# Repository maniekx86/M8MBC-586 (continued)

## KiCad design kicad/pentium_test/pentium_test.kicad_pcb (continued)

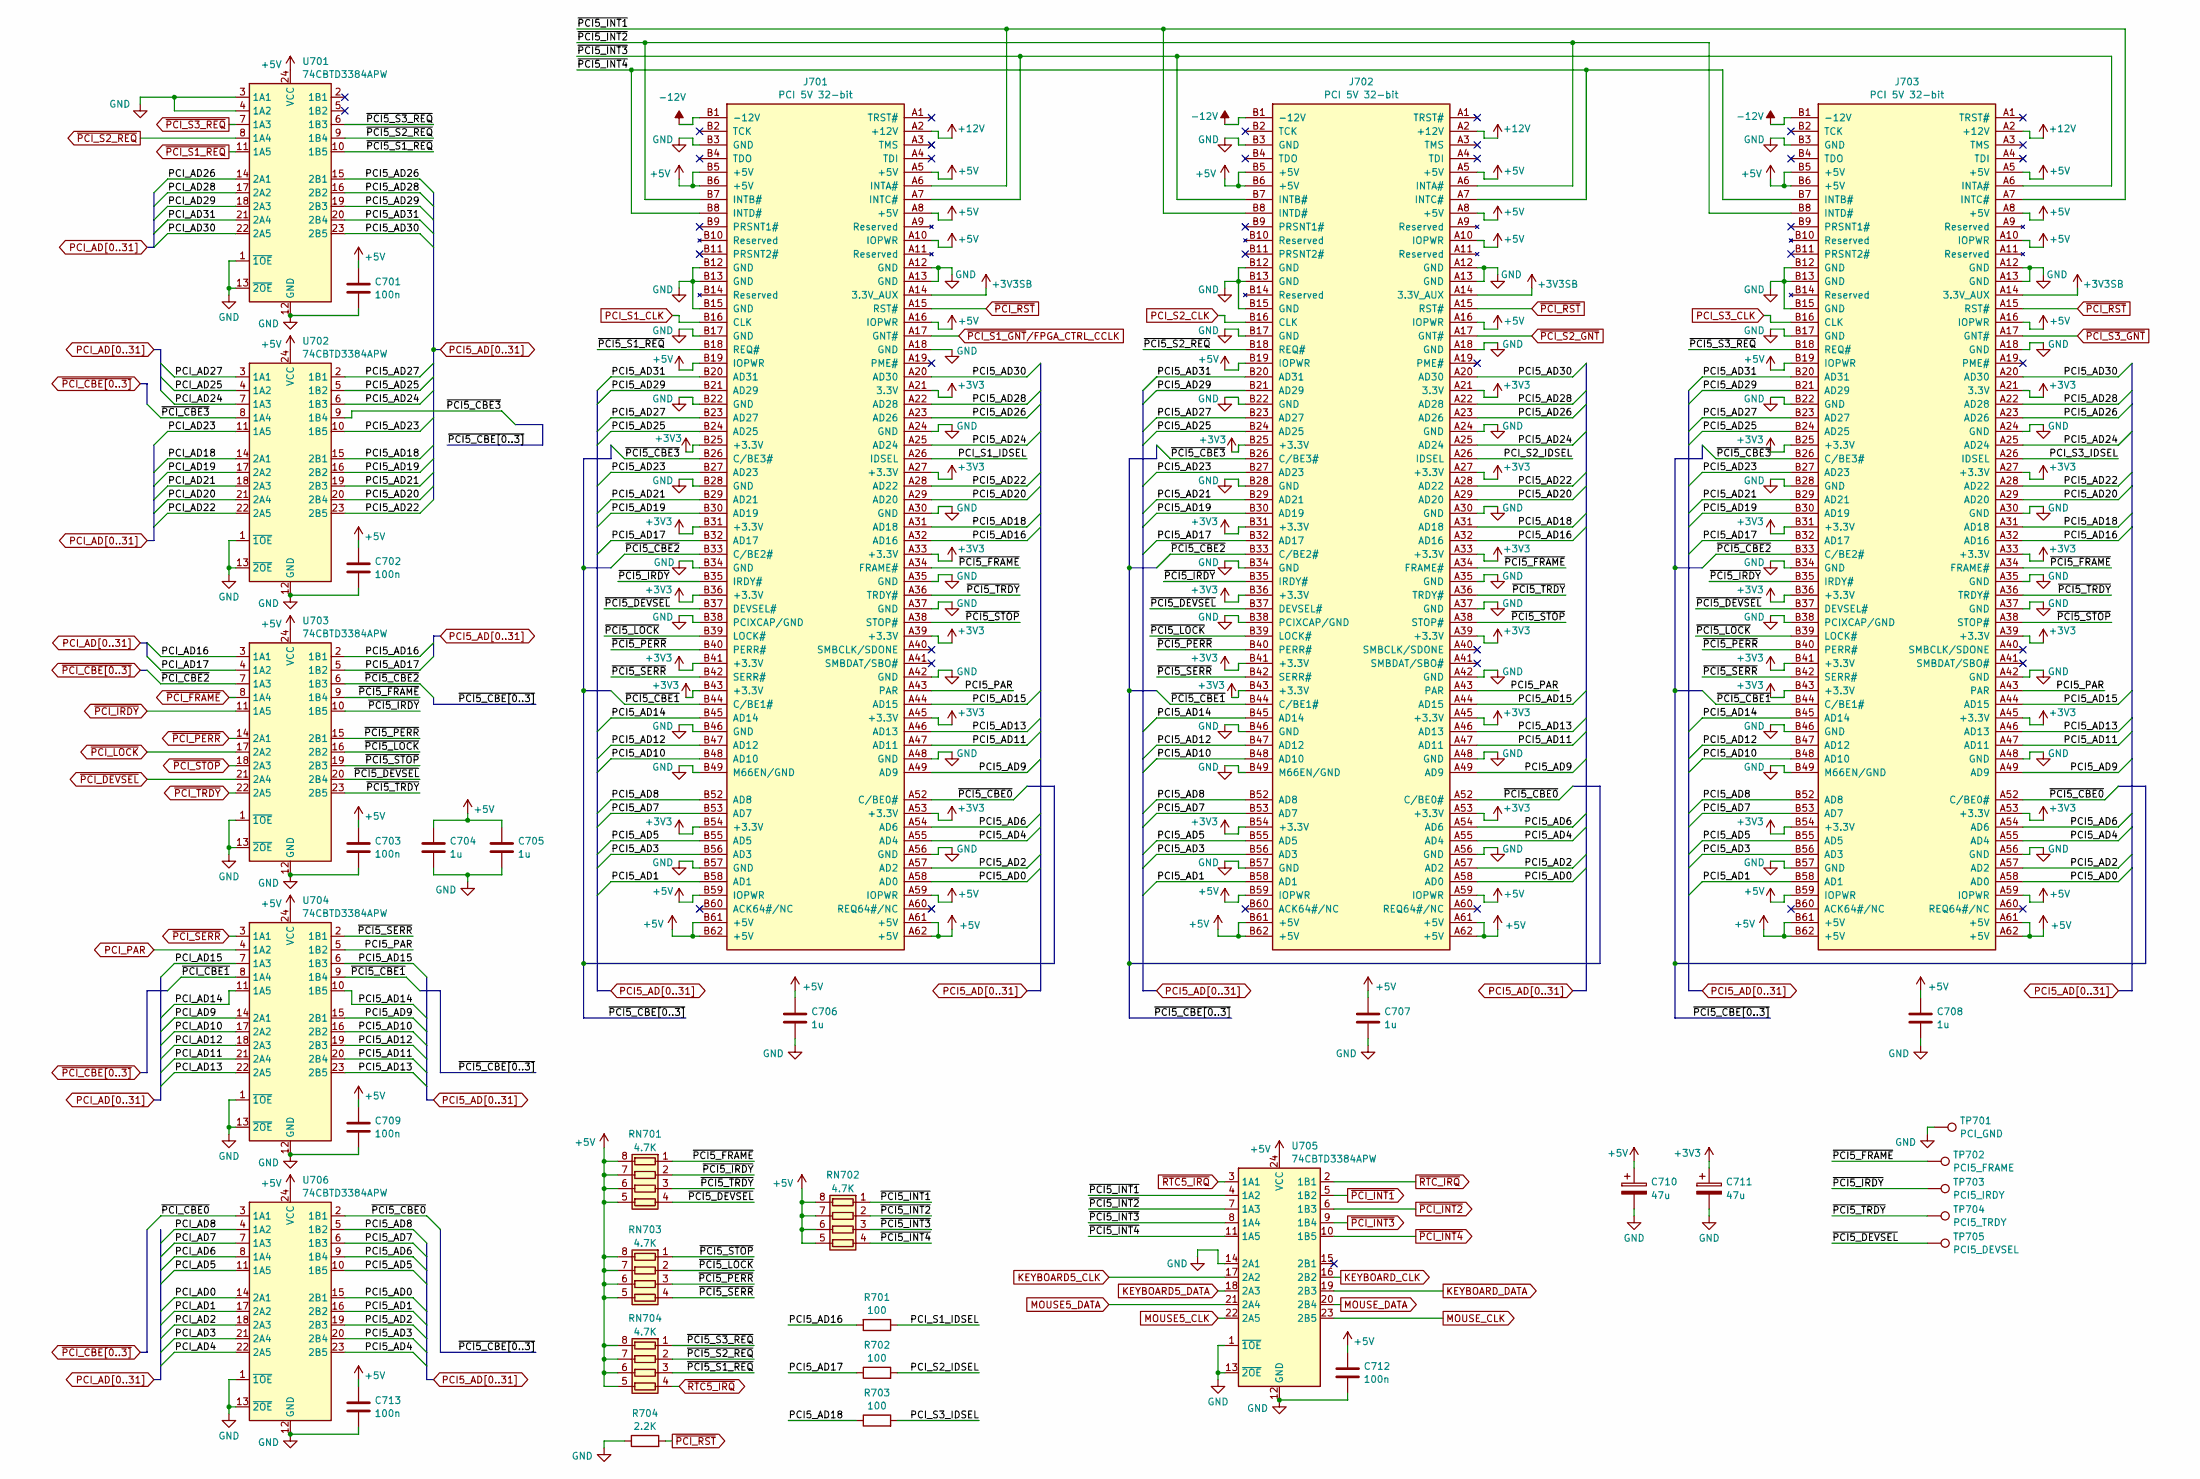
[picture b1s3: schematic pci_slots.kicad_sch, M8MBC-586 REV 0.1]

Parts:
C701, C702, C703, C709, C712, C713: 100n; C_0603_1608Metric
C704, C705, C706, C707, C708: 1u; C_0805_2012Metric
C710, C711: 47u; CP_Radial_D5.0mm_P2.50mm
J701, J702, J703: PCI 5V 32-bit; TE_1-5145154-2; PARTREV E
R701, R702, R703: 100; R_0603_1608Metric
R704: 2.2K; R_0603_1608Metric
RN701, RN702, RN703, RN704: 4.7K; R_Array_Convex_4x0603
TP701: PCI_GND; TestPoint_Pad_D1.0mm
TP702: PCI5_FRAME; TestPoint_Pad_D1.0mm
TP703: PCI5_IRDY; TestPoint_Pad_D1.0mm
TP704: PCI5_TRDY; TestPoint_Pad_D1.0mm
TP705: PCI5_DEVSEL; TestPoint_Pad_D1.0mm
U701, U702, U703, U704, U705, U706: 74CBTD3384APW; TSSOP-24_4.4x7.8mm_P0.65mm

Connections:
+3V3: C711.1, J701.A21 (3.3V), J701.A27 (+3.3V), J701.A33 (+3.3V), J701.A39 (+3.3V), J701.A45 (+3.3V), J701.A53 (+3.3V), J701.B25 (+3.3V), J701.B31 (+3.3V), J701.B36 (+3.3V), J701.B41 (+3.3V), J701.B43 (+3.3V), J701.B54 (+3.3V), J702.A21 (3.3V), J702.A27 (+3.3V), J702.A33 (+3.3V), J702.A39 (+3.3V), J702.A45 (+3.3V), J702.A53 (+3.3V), J702.B25 (+3.3V), J702.B31 (+3.3V), J702.B36 (+3.3V), J702.B41 (+3.3V), J702.B43 (+3.3V), J702.B54 (+3.3V), J703.A21 (3.3V), J703.A27 (+3.3V), J703.A33 (+3.3V), J703.A39 (+3.3V), J703.A45 (+3.3V), J703.A53 (+3.3V), J703.B25 (+3.3V), J703.B31 (+3.3V), J703.B36 (+3.3V), J703.B41 (+3.3V), J703.B43 (+3.3V), J703.B54 (+3.3V); also elsewhere on the board
+3V3SB: J701.A14 (3.3V_AUX), J702.A14 (3.3V_AUX), J703.A14 (3.3V_AUX); also elsewhere on the board
+5V: C701.1, C702.1, C703.1, C704.1, C705.1, C706.1, C707.1, C708.1, C709.1, C710.1, C712.1, C713.1, J701.A5 (+5V), J701.A8 (+5V), J701.A10 (IOPWR), J701.A16 (IOPWR), J701.A59 (IOPWR), J701.A61 (+5V), J701.A62 (+5V), J701.B5 (+5V), J701.B6 (+5V), J701.B19 (IOPWR), J701.B59 (IOPWR), J701.B61 (+5V), J701.B62 (+5V), J702.A5 (+5V), J702.A8 (+5V), J702.A10 (IOPWR), J702.A16 (IOPWR), J702.A59 (IOPWR), J702.A61 (+5V), J702.A62 (+5V), J702.B5 (+5V), J702.B6 (+5V), J702.B19 (IOPWR), J702.B59 (IOPWR), J702.B61 (+5V), J702.B62 (+5V), J703.A5 (+5V), J703.A8 (+5V), J703.A10 (IOPWR), J703.A16 (IOPWR), J703.A59 (IOPWR), J703.A61 (+5V), J703.A62 (+5V), J703.B5 (+5V), J703.B6 (+5V), J703.B19 (IOPWR), J703.B59 (IOPWR), J703.B61 (+5V), J703.B62 (+5V), RN701.5 (R4.2), RN701.6 (R3.2), RN701.7 (R2.2), RN701.8 (R1.2), RN702.5 (R4.2), RN702.6 (R3.2), RN702.7 (R2.2), RN702.8 (R1.2), RN703.5 (R4.2), RN703.6 (R3.2), RN703.7 (R2.2), RN703.8 (R1.2), RN704.5 (R4.2), RN704.6 (R3.2), RN704.7 (R2.2), RN704.8 (R1.2), U701.24 (VCC), U702.24 (VCC), U703.24 (VCC), U704.24 (VCC), U705.24 (VCC), U706.24 (VCC); also elsewhere on the board
+12V: J701.A2 (+12V), J702.A2 (+12V), J703.A2 (+12V); also elsewhere on the board
-12V: J701.B1 (-12V), J702.B1 (-12V), J703.B1 (-12V); also elsewhere on the board
/PCI/PCI5_PAR: J701.A43 (PAR), J702.A43 (PAR), J703.A43 (PAR), U704.5 (1B2)
/PCI/PCI_S1_IDSEL: J701.A26 (IDSEL), R701.1
/PCI/PCI_S2_IDSEL: J702.A26 (IDSEL), R702.2
/PCI/PCI_S3_IDSEL: J703.A26 (IDSEL), R703.2
/PCI/~PCI5_CBE0: J701.A52 (C/BE0#), J702.A52 (C/BE0#), J703.A52 (C/BE0#), U706.2 (1B1)
/PCI/~PCI5_CBE1: J701.B44 (C/BE1#), J702.B44 (C/BE1#), J703.B44 (C/BE1#), U704.9 (1B4)
/PCI/~PCI5_CBE2: J701.B33 (C/BE2#), J702.B33 (C/BE2#), J703.B33 (C/BE2#), U703.6 (1B3)
/PCI/~PCI5_CBE3: J701.B26 (C/BE3#), J702.B26 (C/BE3#), J703.B26 (C/BE3#), U702.9 (1B4)
/PCI/~PCI5_DEVSEL: J701.B37 (DEVSEL#), J702.B37 (DEVSEL#), J703.B37 (DEVSEL#), RN701.4 (R4.1), TP705.1, U703.20 (2B4)
/PCI/~PCI5_FRAME: J701.A34 (FRAME#), J702.A34 (FRAME#), J703.A34 (FRAME#), RN701.1 (R1.1), TP702.1, U703.9 (1B4)
/PCI/~PCI5_INT1: J701.A6 (INTA#), J702.B8 (INTD#), J703.A7 (INTC#), RN702.1 (R1.1), U705.4 (1A2)
/PCI/~PCI5_INT2: J701.B7 (INTB#), J702.A6 (INTA#), J703.B8 (INTD#), RN702.2 (R2.1), U705.7 (1A3)
/PCI/~PCI5_INT3: J701.A7 (INTC#), J702.B7 (INTB#), J703.A6 (INTA#), RN702.3 (R3.1), U705.8 (1A4)
/PCI/~PCI5_INT4: J701.B8 (INTD#), J702.A7 (INTC#), J703.B7 (INTB#), RN702.4 (R4.1), U705.11 (1A5)
/PCI/~PCI5_IRDY: J701.B35 (IRDY#), J702.B35 (IRDY#), J703.B35 (IRDY#), RN701.2 (R2.1), TP703.1, U703.10 (1B5)
/PCI/~PCI5_LOCK: J701.B39 (LOCK#), J702.B39 (LOCK#), J703.B39 (LOCK#), RN703.2 (R2.1), U703.16 (2B2)
/PCI/~PCI5_PERR: J701.B40 (PERR#), J702.B40 (PERR#), J703.B40 (PERR#), RN703.3 (R3.1), U703.15 (2B1)
/PCI/~PCI5_S1_REQ: J701.B18 (REQ#), RN704.3 (R3.1), U701.10 (1B5)
/PCI/~PCI5_S2_REQ: J702.B18 (REQ#), RN704.2 (R2.1), U701.9 (1B4)
/PCI/~PCI5_S3_REQ: J703.B18 (REQ#), RN704.1 (R1.1), U701.6 (1B3)
/PCI/~PCI5_SERR: J701.B42 (SERR#), J702.B42 (SERR#), J703.B42 (SERR#), RN703.4 (R4.1), U704.2 (1B1)
/PCI/~PCI5_STOP: J701.A38 (STOP#), J702.A38 (STOP#), J703.A38 (STOP#), RN703.1 (R1.1), U703.19 (2B3)
/PCI/~PCI5_TRDY: J701.A36 (TRDY#), J702.A36 (TRDY#), J703.A36 (TRDY#), RN701.3 (R3.1), TP704.1, U703.23 (2B5)
GND: C701.2, C702.2, C703.2, C704.2, C705.2, C706.2, C707.2, C708.2, C709.2, C710.2, C711.2, C712.2, C713.2, J701.A12 (GND), J701.A13 (GND), J701.A18 (GND), J701.A24 (GND), J701.A30 (GND), J701.A35 (GND), J701.A37 (GND), J701.A42 (GND), J701.A48 (GND), J701.A56 (GND), J701.B3 (GND), J701.B12 (GND), J701.B13 (GND), J701.B15 (GND), J701.B17 (GND), J701.B22 (GND), J701.B28 (GND), J701.B34 (GND), J701.B38 (PCIXCAP/GND), J701.B46 (GND), J701.B49 (M66EN/GND), J701.B57 (GND), J702.A12 (GND), J702.A13 (GND), J702.A18 (GND), J702.A24 (GND), J702.A30 (GND), J702.A35 (GND), J702.A37 (GND), J702.A42 (GND), J702.A48 (GND), J702.A56 (GND), J702.B3 (GND), J702.B12 (GND), J702.B13 (GND), J702.B15 (GND), J702.B17 (GND), J702.B22 (GND), J702.B28 (GND), J702.B34 (GND), J702.B38 (PCIXCAP/GND), J702.B46 (GND), J702.B49 (M66EN/GND), J702.B57 (GND), J703.A12 (GND), J703.A13 (GND), J703.A18 (GND), J703.A24 (GND), J703.A30 (GND), J703.A35 (GND), J703.A37 (GND), J703.A42 (GND), J703.A48 (GND), J703.A56 (GND), J703.B3 (GND), J703.B12 (GND), J703.B13 (GND), J703.B15 (GND), J703.B17 (GND), J703.B22 (GND), J703.B28 (GND), J703.B34 (GND), J703.B38 (PCIXCAP/GND), J703.B46 (GND), J703.B49 (M66EN/GND), J703.B57 (GND), R704.1, TP701.1, U701.1 (~1OE), U701.3 (1A1), U701.4 (1A2), U701.12 (GND), U701.13 (~2OE), U702.1 (~1OE), U702.12 (GND), U702.13 (~2OE), U703.1 (~1OE), U703.12 (GND), U703.13 (~2OE), U704.1 (~1OE), U704.12 (GND), U704.13 (~2OE), U705.1 (~1OE), U705.12 (GND), U705.13 (~2OE), U705.14 (2A1), U706.1 (~1OE), U706.12 (GND), U706.13 (~2OE); also elsewhere on the board
KEYBOARD5_CLK: U705.17 (2A2); also elsewhere on the board
KEYBOARD5_DATA: U705.18 (2A3); also elsewhere on the board
KEYBOARD_CLK: U705.16 (2B2); also elsewhere on the board
KEYBOARD_DATA: U705.19 (2B3); also elsewhere on the board
MOUSE5_CLK: U705.22 (2A5); also elsewhere on the board
MOUSE5_DATA: U705.21 (2A4); also elsewhere on the board
MOUSE_CLK: U705.23 (2B5); also elsewhere on the board
MOUSE_DATA: U705.20 (2B4); also elsewhere on the board
PCI5_AD0: J701.A58 (AD0), J702.A58 (AD0), J703.A58 (AD0), U706.15 (2B1)
PCI5_AD1: J701.B58 (AD1), J702.B58 (AD1), J703.B58 (AD1), U706.16 (2B2)
PCI5_AD2: J701.A57 (AD2), J702.A57 (AD2), J703.A57 (AD2), U706.19 (2B3)
PCI5_AD3: J701.B56 (AD3), J702.B56 (AD3), J703.B56 (AD3), U706.20 (2B4)
PCI5_AD4: J701.A55 (AD4), J702.A55 (AD4), J703.A55 (AD4), U706.23 (2B5)
PCI5_AD5: J701.B55 (AD5), J702.B55 (AD5), J703.B55 (AD5), U706.10 (1B5)
PCI5_AD6: J701.A54 (AD6), J702.A54 (AD6), J703.A54 (AD6), U706.9 (1B4)
PCI5_AD7: J701.B53 (AD7), J702.B53 (AD7), J703.B53 (AD7), U706.6 (1B3)
PCI5_AD8: J701.B52 (AD8), J702.B52 (AD8), J703.B52 (AD8), U706.5 (1B2)
PCI5_AD9: J701.A49 (AD9), J702.A49 (AD9), J703.A49 (AD9), U704.15 (2B1)
PCI5_AD10: J701.B48 (AD10), J702.B48 (AD10), J703.B48 (AD10), U704.16 (2B2)
PCI5_AD11: J701.A47 (AD11), J702.A47 (AD11), J703.A47 (AD11), U704.20 (2B4)
PCI5_AD12: J701.B47 (AD12), J702.B47 (AD12), J703.B47 (AD12), U704.19 (2B3)
PCI5_AD13: J701.A46 (AD13), J702.A46 (AD13), J703.A46 (AD13), U704.23 (2B5)
PCI5_AD14: J701.B45 (AD14), J702.B45 (AD14), J703.B45 (AD14), U704.10 (1B5)
PCI5_AD15: J701.A44 (AD15), J702.A44 (AD15), J703.A44 (AD15), U704.6 (1B3)
PCI5_AD16: J701.A32 (AD16), J702.A32 (AD16), J703.A32 (AD16), R701.2, U703.2 (1B1)
PCI5_AD17: J701.B32 (AD17), J702.B32 (AD17), J703.B32 (AD17), R702.1, U703.5 (1B2)
PCI5_AD18: J701.A31 (AD18), J702.A31 (AD18), J703.A31 (AD18), R703.1, U702.15 (2B1)
PCI5_AD19: J701.B30 (AD19), J702.B30 (AD19), J703.B30 (AD19), U702.16 (2B2)
PCI5_AD20: J701.A29 (AD20), J702.A29 (AD20), J703.A29 (AD20), U702.20 (2B4)
PCI5_AD21: J701.B29 (AD21), J702.B29 (AD21), J703.B29 (AD21), U702.19 (2B3)
PCI5_AD22: J701.A28 (AD22), J702.A28 (AD22), J703.A28 (AD22), U702.23 (2B5)
PCI5_AD23: J701.B27 (AD23), J702.B27 (AD23), J703.B27 (AD23), U702.10 (1B5)
PCI5_AD24: J701.A25 (AD24), J702.A25 (AD24), J703.A25 (AD24), U702.6 (1B3)
PCI5_AD25: J701.B24 (AD25), J702.B24 (AD25), J703.B24 (AD25), U702.5 (1B2)
PCI5_AD26: J701.A23 (AD26), J702.A23 (AD26), J703.A23 (AD26), U701.15 (2B1)
PCI5_AD27: J701.B23 (AD27), J702.B23 (AD27), J703.B23 (AD27), U702.2 (1B1)
PCI5_AD28: J701.A22 (AD28), J702.A22 (AD28), J703.A22 (AD28), U701.16 (2B2)
PCI5_AD29: J701.B21 (AD29), J702.B21 (AD29), J703.B21 (AD29), U701.19 (2B3)
PCI5_AD30: J701.A20 (AD30), J702.A20 (AD30), J703.A20 (AD30), U701.23 (2B5)
PCI5_AD31: J701.B20 (AD31), J702.B20 (AD31), J703.B20 (AD31), U701.20 (2B4)
PCI_AD0: U706.14 (2A1); also elsewhere on the board
PCI_AD1: U706.17 (2A2); also elsewhere on the board
PCI_AD2: U706.18 (2A3); also elsewhere on the board
PCI_AD3: U706.21 (2A4); also elsewhere on the board
PCI_AD4: U706.22 (2A5); also elsewhere on the board
PCI_AD5: U706.11 (1A5); also elsewhere on the board
PCI_AD6: U706.8 (1A4); also elsewhere on the board
PCI_AD7: U706.7 (1A3); also elsewhere on the board
PCI_AD8: U706.4 (1A2); also elsewhere on the board
PCI_AD9: U704.14 (2A1); also elsewhere on the board
PCI_AD10: U704.17 (2A2); also elsewhere on the board
PCI_AD11: U704.21 (2A4); also elsewhere on the board
PCI_AD12: U704.18 (2A3); also elsewhere on the board
PCI_AD13: U704.22 (2A5); also elsewhere on the board
PCI_AD14: U704.11 (1A5); also elsewhere on the board
PCI_AD15: U704.7 (1A3); also elsewhere on the board
PCI_AD16: U703.3 (1A1); also elsewhere on the board
PCI_AD17: U703.4 (1A2); also elsewhere on the board
PCI_AD18: U702.14 (2A1); also elsewhere on the board
PCI_AD19: U702.17 (2A2); also elsewhere on the board
PCI_AD20: U702.21 (2A4); also elsewhere on the board
PCI_AD21: U702.18 (2A3); also elsewhere on the board
PCI_AD22: U702.22 (2A5); also elsewhere on the board
PCI_AD23: U702.11 (1A5); also elsewhere on the board
PCI_AD24: U702.7 (1A3); also elsewhere on the board
PCI_AD25: U702.4 (1A2); also elsewhere on the board
PCI_AD26: U701.14 (2A1); also elsewhere on the board
PCI_AD27: U702.3 (1A1); also elsewhere on the board
PCI_AD28: U701.17 (2A2); also elsewhere on the board
PCI_AD29: U701.18 (2A3); also elsewhere on the board
PCI_AD30: U701.22 (2A5); also elsewhere on the board
PCI_AD31: U701.21 (2A4); also elsewhere on the board
PCI_PAR: U704.4 (1A2); also elsewhere on the board
PCI_S1_CLK: J701.B16 (CLK); also elsewhere on the board
PCI_S2_CLK: J702.B16 (CLK); also elsewhere on the board
PCI_S3_CLK: J703.B16 (CLK); also elsewhere on the board
~PCI_CBE0: U706.3 (1A1); also elsewhere on the board
~PCI_CBE1: U704.8 (1A4); also elsewhere on the board
~PCI_CBE2: U703.7 (1A3); also elsewhere on the board
~PCI_CBE3: U702.8 (1A4); also elsewhere on the board
~PCI_DEVSEL: U703.21 (2A4); also elsewhere on the board
~PCI_FRAME: U703.8 (1A4); also elsewhere on the board
~PCI_INT1: U705.5 (1B2); also elsewhere on the board
~PCI_INT2: U705.6 (1B3); also elsewhere on the board
~PCI_INT3: U705.9 (1B4); also elsewhere on the board
~PCI_INT4: U705.10 (1B5); also elsewhere on the board
~PCI_IRDY: U703.11 (1A5); also elsewhere on the board
~PCI_LOCK: U703.17 (2A2); also elsewhere on the board
~PCI_PERR: U703.14 (2A1); also elsewhere on the board
~PCI_RST: J701.A15 (RST#), J702.A15 (RST#), J703.A15 (RST#), R704.2; also elsewhere on the board
~PCI_S1_GNT/FPGA_CTRL_CCLK: J701.A17 (GNT#); also elsewhere on the board
~PCI_S1_REQ: U701.11 (1A5); also elsewhere on the board
~PCI_S2_GNT: J702.A17 (GNT#); also elsewhere on the board
~PCI_S2_REQ: U701.8 (1A4); also elsewhere on the board
~PCI_S3_GNT: J703.A17 (GNT#); also elsewhere on the board
~PCI_S3_REQ: U701.7 (1A3); also elsewhere on the board
~PCI_SERR: U704.3 (1A1); also elsewhere on the board
~PCI_STOP: U703.18 (2A3); also elsewhere on the board
~PCI_TRDY: U703.22 (2A5); also elsewhere on the board
~RTC5_IRQ: RN704.4 (R4.1), U705.3 (1A1); also elsewhere on the board
~RTC_IRQ: U705.2 (1B1); also elsewhere on the board

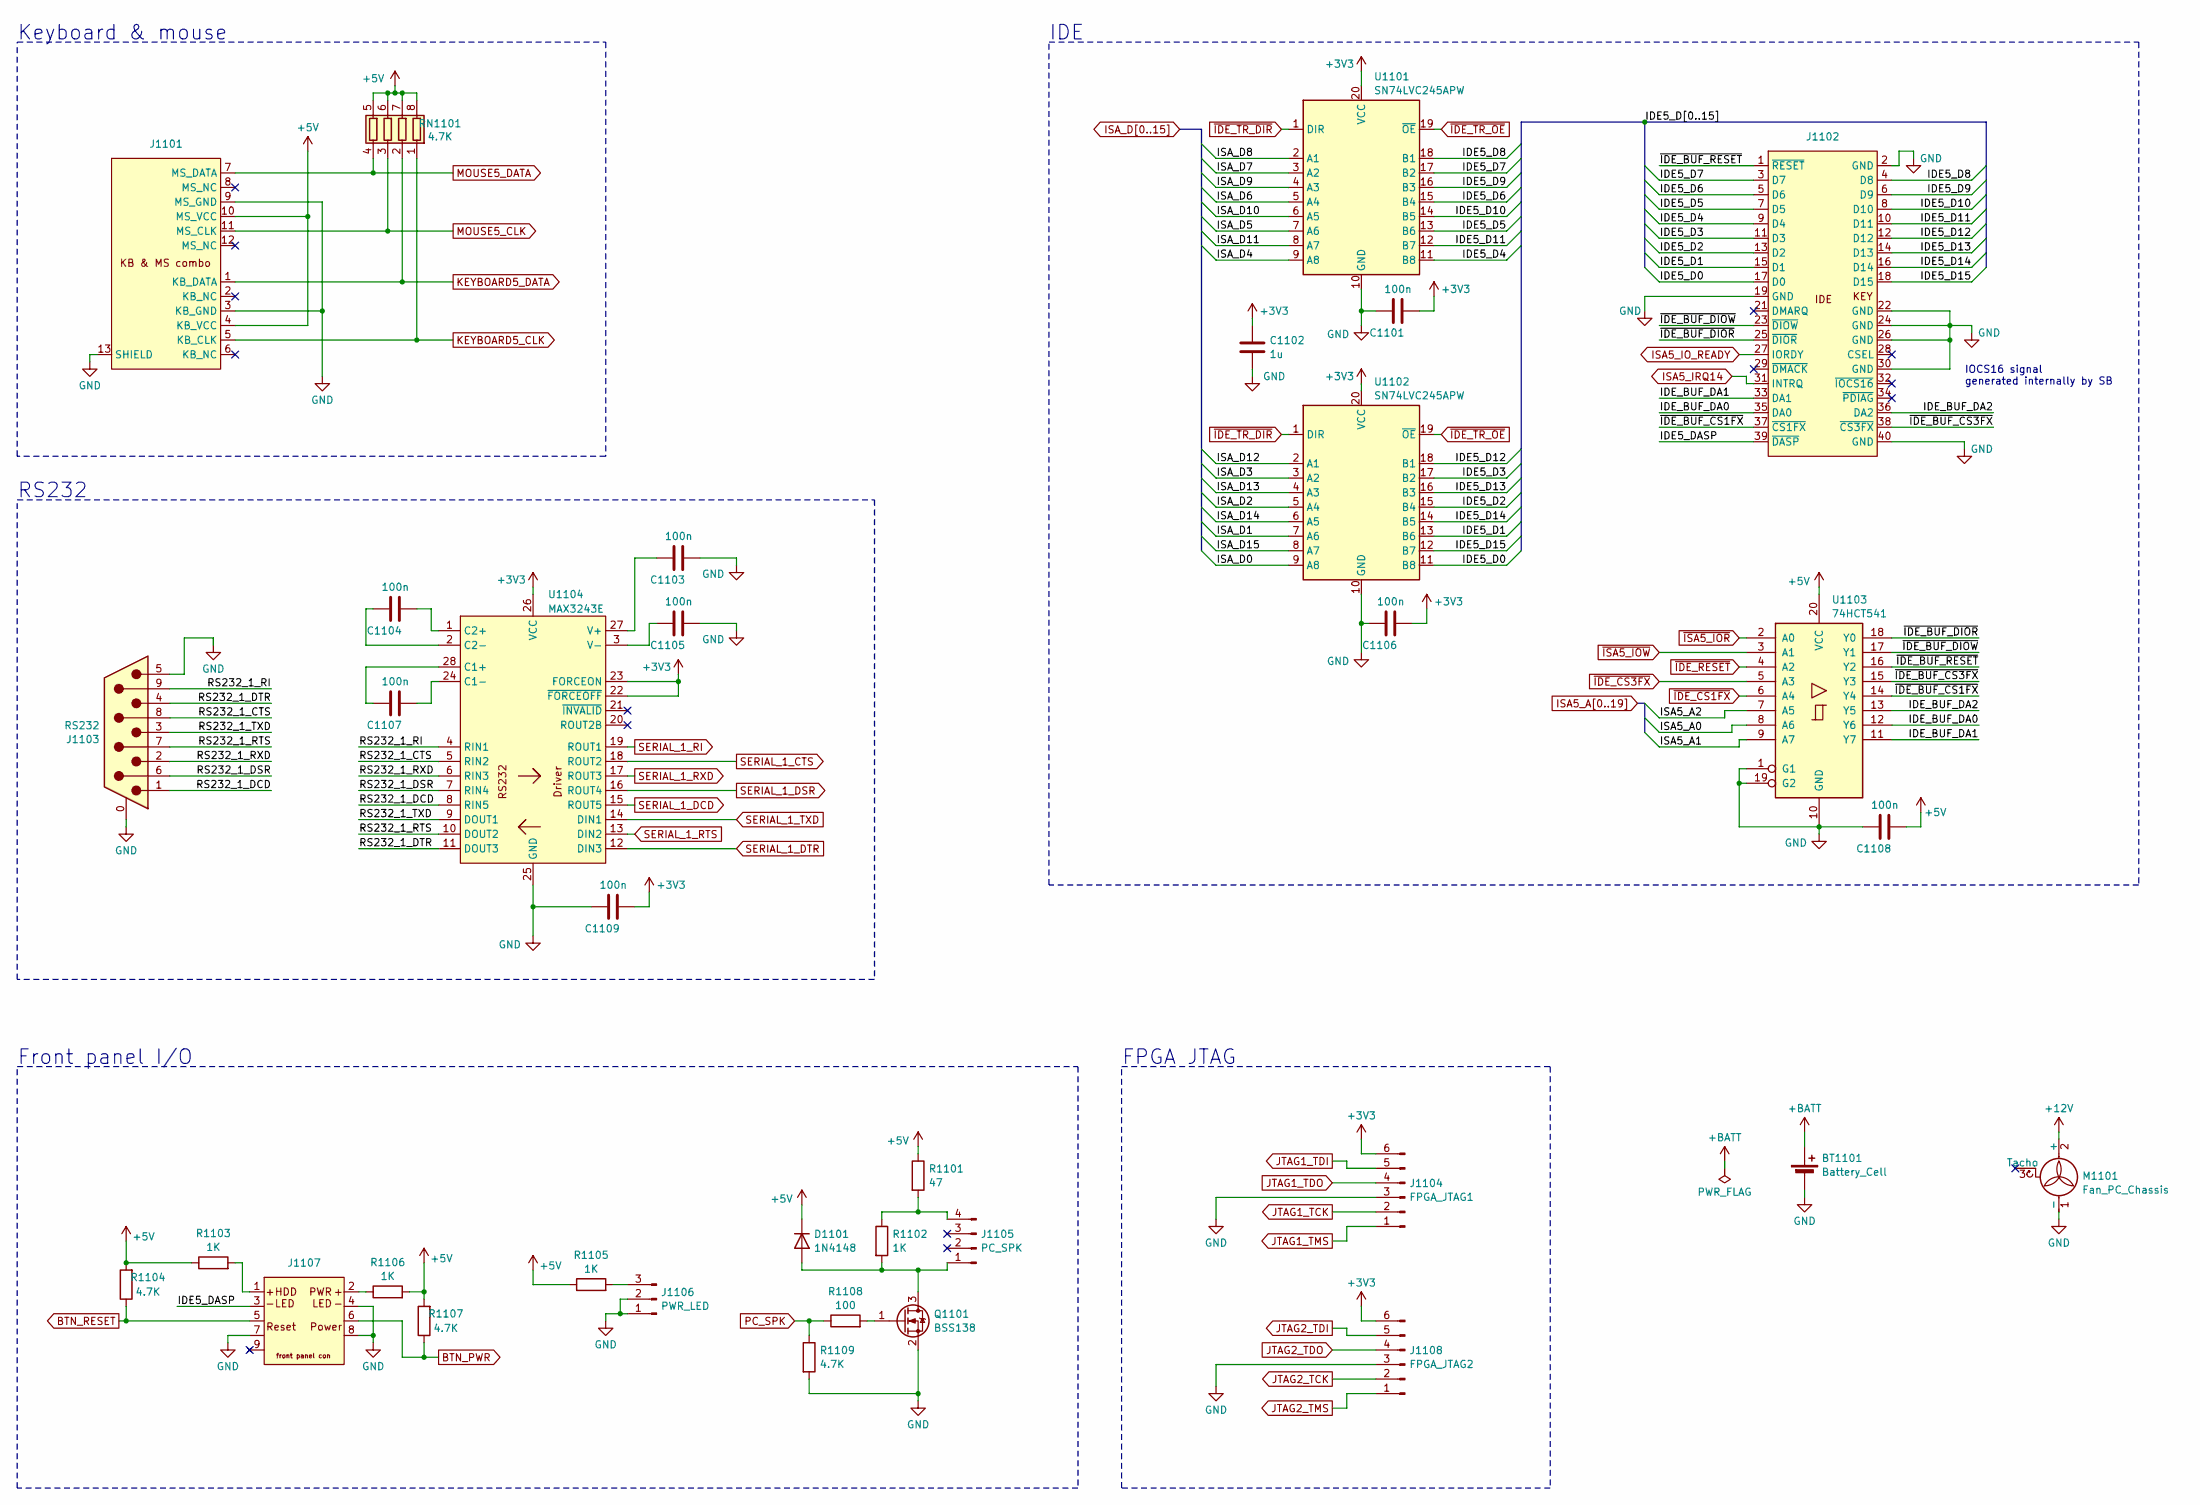
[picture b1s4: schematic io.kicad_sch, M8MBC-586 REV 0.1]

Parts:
BT1101: Battery_Cell; BatteryHolder_MYOUNG_BS-07-A1BJ001_CR2032
C1101, C1103, C1104, C1105, C1106, C1107, C1108, C1109: 100n; C_0603_1608Metric
C1102: 1u; C_0805_2012Metric
D1101: 1N4148; D_A-405_P7.62mm_Horizontal
J1101: MH11061-D2_kb_ms_combo
J1102: idc_02x20_IDE
J1103: RS232; DSUB-9_Pins_Horizontal_P2.77x2.84mm_EdgePinOffset7.70mm_Hou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
J1104: FPGA_JTAG1; PinHeader_1x06_P2.54mm_Vertical
J1105: PC_SPK; PinHeader_1x04_P2.54mm_Vertical
J1106: PWR_LED; PinHeader_1x03_P2.54mm_Vertical
J1107: front_panel_2x05
J1108: FPGA_JTAG2; PinHeader_1x06_P2.54mm_Vertical
M1101: Fan_PC_Chassis; Molex_KK-254_AE-6410-03A_1x03_P2.54mm_Vertical
Q1101: BSS138; SOT-23
R1101: 47; R_Axial_DIN0207_L6.3mm_D2.5mm_P7.62mm_Horizontal
R1102, R1103, R1105, R1106: 1K; R_0603_1608Metric
R1104, R1107, R1109: 4.7K; R_0603_1608Metric
R1108: 100; R_0603_1608Metric
RN1101: 4.7K; R_Array_Convex_4x0603
U1101, U1102: SN74LVC245APW; TSSOP-20_4.4x6.5mm_P0.65mm
U1103: 74HCT541; TSSOP-20_4.4x6.5mm_P0.65mm
U1104: MAX3243E; SSOP-28_5.3x10.2mm_P0.65mm

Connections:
+3V3: C1101.2, C1102.1, C1106.2, C1109.2, J1104.6, J1108.6, U1101.20 (VCC), U1102.20 (VCC), U1104.22 (~FORCEOFF), U1104.23 (FORCEON), U1104.26 (VCC); also elsewhere on the board
+5V: C1108.2, D1101.1 (K), J1101.4 (KB_VCC), J1101.10 (MS_VCC), R1101.1, R1103.1, R1104.2, R1105.1, R1106.2, R1107.2, RN1101.5 (R4.2), RN1101.6 (R3.2), RN1101.7 (R2.2), RN1101.8 (R1.2), U1103.20 (VCC); also elsewhere on the board
+12V: M1101.2 (+); also elsewhere on the board
+BATT: BT1101.1 (+); also elsewhere on the board
/IO/IDE5_D0: J1102.17 (D0), U1102.11 (B8)
/IO/IDE5_D1: J1102.15 (D1), U1102.13 (B6)
/IO/IDE5_D2: J1102.13 (D2), U1102.15 (B4)
/IO/IDE5_D3: J1102.11 (D3), U1102.17 (B2)
/IO/IDE5_D4: J1102.9 (D4), U1101.11 (B8)
/IO/IDE5_D5: J1102.7 (D5), U1101.13 (B6)
/IO/IDE5_D6: J1102.5 (D6), U1101.15 (B4)
/IO/IDE5_D7: J1102.3 (D7), U1101.17 (B2)
/IO/IDE5_D8: J1102.4 (D8), U1101.18 (B1)
/IO/IDE5_D9: J1102.6 (D9), U1101.16 (B3)
/IO/IDE5_D10: J1102.8 (D10), U1101.14 (B5)
/IO/IDE5_D11: J1102.10 (D11), U1101.12 (B7)
/IO/IDE5_D12: J1102.12 (D12), U1102.18 (B1)
/IO/IDE5_D13: J1102.14 (D13), U1102.16 (B3)
/IO/IDE5_D14: J1102.16 (D14), U1102.14 (B5)
/IO/IDE5_D15: J1102.18 (D15), U1102.12 (B7)
/IO/IDE5_DASP: J1102.39 (~DASP), J1107.3
/IO/IDE_BUF_DA0: J1102.35 (DA0), U1103.12 (Y6)
/IO/IDE_BUF_DA1: J1102.33 (DA1), U1103.11 (Y7)
/IO/IDE_BUF_DA2: J1102.36 (DA2), U1103.13 (Y5)
/IO/RS232_1_CTS: J1103.8, U1104.5 (RIN2)
/IO/RS232_1_DCD: J1103.1, U1104.8 (RIN5)
/IO/RS232_1_DSR: J1103.6, U1104.7 (RIN4)
/IO/RS232_1_DTR: J1103.4, U1104.11 (DOUT3)
/IO/RS232_1_RI: J1103.9, U1104.4 (RIN1)
/IO/RS232_1_RTS: J1103.7, U1104.10 (DOUT2)
/IO/RS232_1_RXD: J1103.2, U1104.6 (RIN3)
/IO/RS232_1_TXD: J1103.3, U1104.9 (DOUT1)
/IO/~IDE_BUF_CS1FX: J1102.37 (~CS1FX), U1103.14 (Y4)
/IO/~IDE_BUF_CS3FX: J1102.38 (~CS3FX), U1103.15 (Y3)
/IO/~IDE_BUF_DIOR: J1102.25 (~DIOR), U1103.18 (Y0)
/IO/~IDE_BUF_DIOW: J1102.23 (~DIOW), U1103.17 (Y1)
/IO/~IDE_BUF_RESET: J1102.1 (~RESET), U1103.16 (Y2)
BTN_PWR: J1107.6, R1107.1; also elsewhere on the board
BTN_RESET: J1107.5, R1104.1; also elsewhere on the board
GND: BT1101.2 (-), C1101.1, C1102.2, C1103.2, C1105.2, C1106.1, C1108.1, C1109.1, J1101.3 (KB_GND), J1101.9 (MS_GND), J1101.13 (SHIELD), J1102.2 (GND), J1102.19 (GND), J1102.22 (GND), J1102.24 (GND), J1102.26 (GND), J1102.30 (GND), J1102.40 (GND), J1103.0 (PAD), J1103.5, J1104.3, J1106.1, J1106.2, J1107.4, J1107.7, J1107.8, J1108.3, M1101.1 (-), Q1101.2 (S), R1109.2, U1101.10 (GND), U1102.10 (GND), U1103.1 (G1), U1103.10 (GND), U1103.19 (G2), U1104.25 (GND); also elsewhere on the board
ISA5_A0: U1103.8 (A6); also elsewhere on the board
ISA5_A1: U1103.9 (A7); also elsewhere on the board
ISA5_A2: U1103.7 (A5); also elsewhere on the board
ISA5_IO_READY: J1102.27 (IORDY); also elsewhere on the board
ISA5_IRQ14: J1102.31 (INTRQ); also elsewhere on the board
ISA_D0: U1102.9 (A8); also elsewhere on the board
ISA_D1: U1102.7 (A6); also elsewhere on the board
ISA_D2: U1102.5 (A4); also elsewhere on the board
ISA_D3: U1102.3 (A2); also elsewhere on the board
ISA_D4: U1101.9 (A8); also elsewhere on the board
ISA_D5: U1101.7 (A6); also elsewhere on the board
ISA_D6: U1101.5 (A4); also elsewhere on the board
ISA_D7: U1101.3 (A2); also elsewhere on the board
ISA_D8: U1101.2 (A1); also elsewhere on the board
ISA_D9: U1101.4 (A3); also elsewhere on the board
ISA_D10: U1101.6 (A5); also elsewhere on the board
ISA_D11: U1101.8 (A7); also elsewhere on the board
ISA_D12: U1102.2 (A1); also elsewhere on the board
ISA_D13: U1102.4 (A3); also elsewhere on the board
ISA_D14: U1102.6 (A5); also elsewhere on the board
ISA_D15: U1102.8 (A7); also elsewhere on the board
JTAG1_TCK: J1104.2; also elsewhere on the board
JTAG1_TDI: J1104.5; also elsewhere on the board
JTAG1_TDO: J1104.4; also elsewhere on the board
JTAG1_TMS: J1104.1; also elsewhere on the board
JTAG2_TCK: J1108.2; also elsewhere on the board
JTAG2_TDI: J1108.5; also elsewhere on the board
JTAG2_TDO: J1108.4; also elsewhere on the board
JTAG2_TMS: J1108.1; also elsewhere on the board
KEYBOARD5_CLK: J1101.5 (KB_CLK), RN1101.1 (R1.1); also elsewhere on the board
KEYBOARD5_DATA: J1101.1 (KB_DATA), RN1101.2 (R2.1); also elsewhere on the board
MOUSE5_CLK: J1101.11 (MS_CLK), RN1101.3 (R3.1); also elsewhere on the board
MOUSE5_DATA: J1101.7 (MS_DATA), RN1101.4 (R4.1); also elsewhere on the board
unnamed: D1101.2 (A), J1105.1, Q1101.3 (D), R1102.2
unnamed: J1105.4, R1101.2, R1102.1
unnamed: J1106.3, R1105.2
unnamed: J1107.1, R1103.2
unnamed: J1107.2, R1106.1
unnamed: Q1101.1 (G), R1108.2
unnamed: C1107.1, U1104.28 (C1+)
unnamed: C1107.2, U1104.24 (C1-)
unnamed: C1104.2, U1104.1 (C2+)
unnamed: C1104.1, U1104.2 (C2-)
unnamed: C1103.1, U1104.27 (V+)
unnamed: C1105.1, U1104.3 (V-)
PC_SPK: R1108.1, R1109.1; also elsewhere on the board
SERIAL_1_CTS: U1104.18 (ROUT2); also elsewhere on the board
SERIAL_1_DCD: U1104.15 (ROUT5); also elsewhere on the board
SERIAL_1_DSR: U1104.16 (ROUT4); also elsewhere on the board
SERIAL_1_DTR: U1104.12 (DIN3); also elsewhere on the board
SERIAL_1_RI: U1104.19 (ROUT1); also elsewhere on the board
SERIAL_1_RTS: U1104.13 (DIN2); also elsewhere on the board
SERIAL_1_RXD: U1104.17 (ROUT3); also elsewhere on the board
SERIAL_1_TXD: U1104.14 (DIN1); also elsewhere on the board
~IDE_CS1FX: U1103.6 (A4); also elsewhere on the board
~IDE_CS3FX: U1103.5 (A3); also elsewhere on the board
~IDE_RESET: U1103.4 (A2); also elsewhere on the board
~IDE_TR_DIR: U1101.1 (DIR), U1102.1 (DIR); also elsewhere on the board
~IDE_TR_OE: U1101.19 (~OE), U1102.19 (~OE); also elsewhere on the board
~ISA5_IOR: U1103.2 (A0); also elsewhere on the board
~ISA5_IOW: U1103.3 (A1); also elsewhere on the board

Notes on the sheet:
FPGA JTAG
IDE
IOCS16 signal generated internally by SB
Keyboard & mouse
RS232
Front panel I/O
